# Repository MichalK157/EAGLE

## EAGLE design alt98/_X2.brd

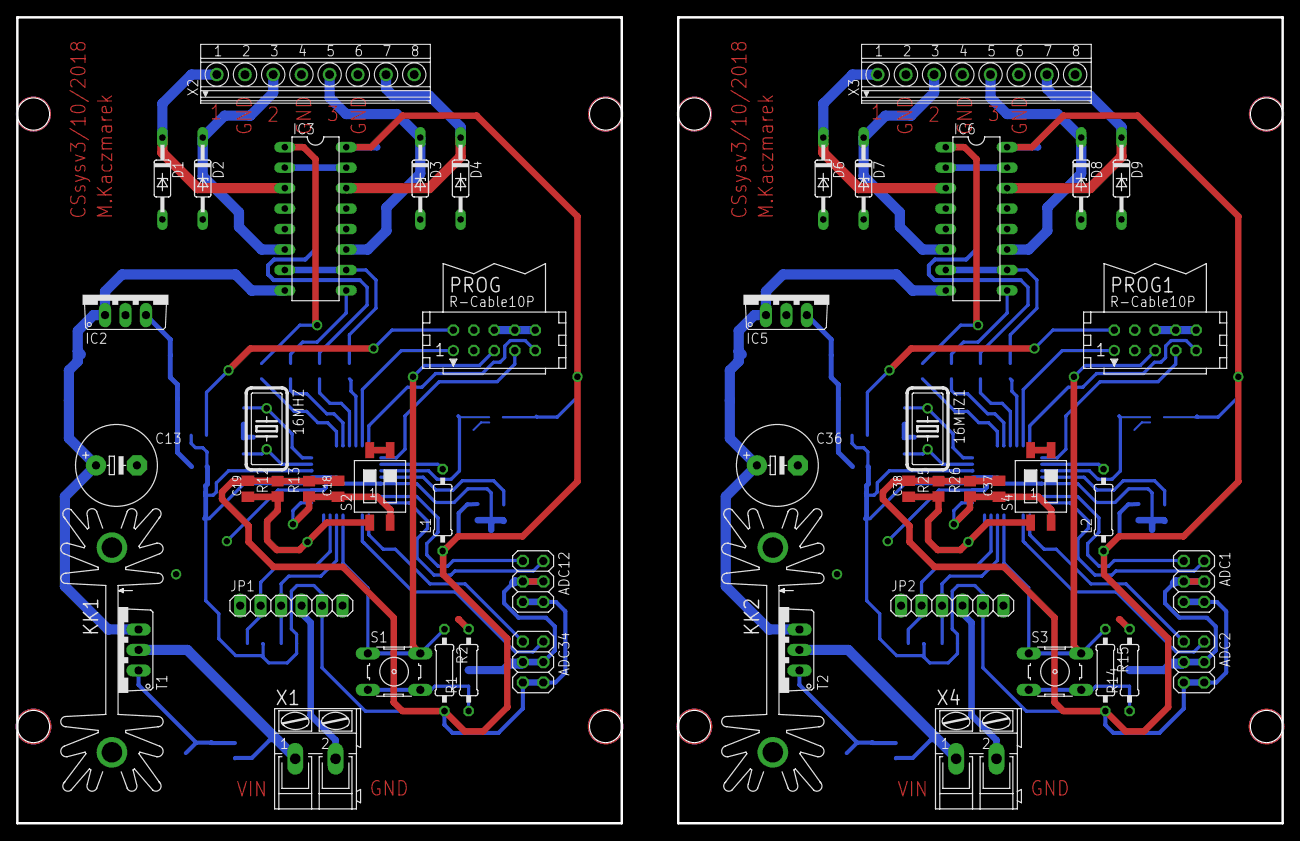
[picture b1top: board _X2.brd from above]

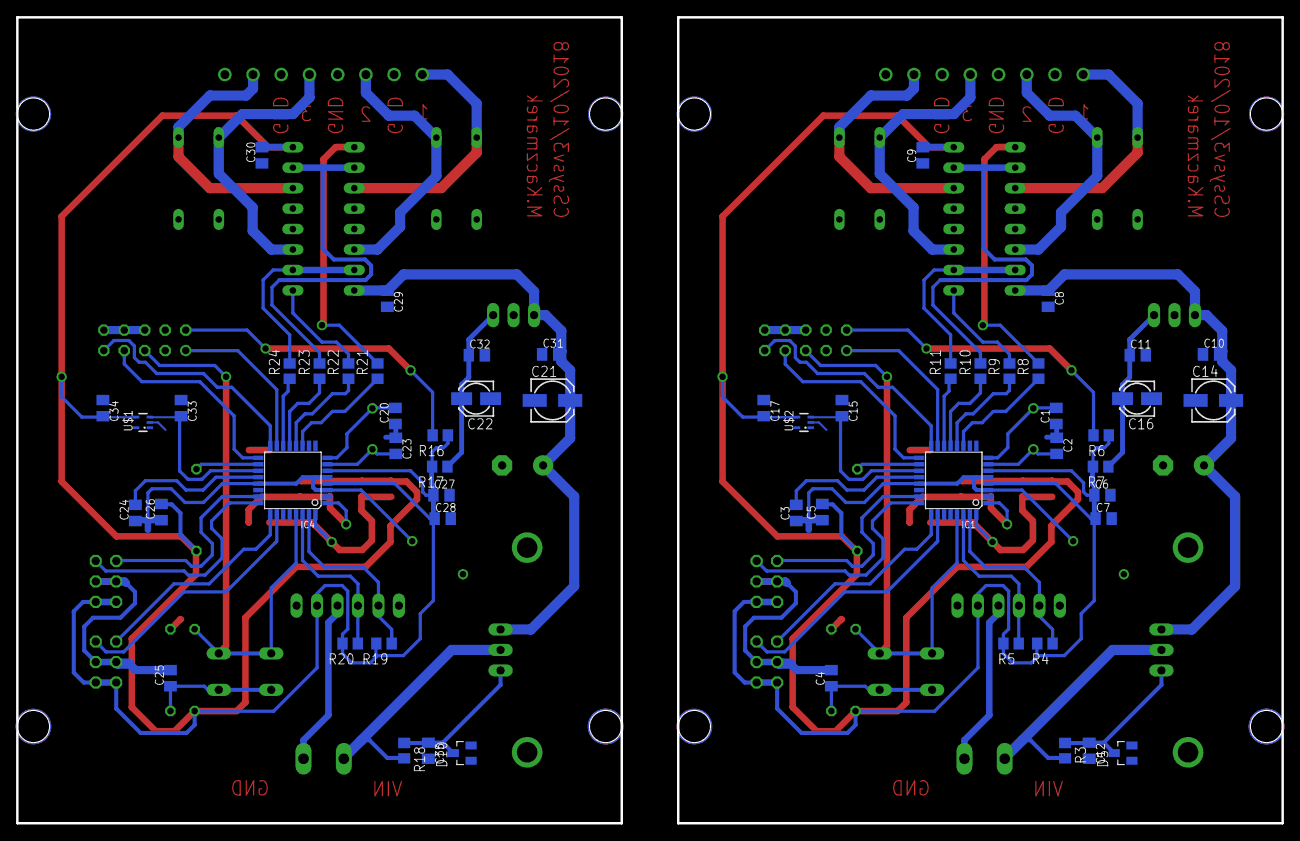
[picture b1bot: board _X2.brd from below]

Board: 2 copper layers, 157.0 x 100.0 mm, 106 parts (56 on the bottom side), 74 nets.

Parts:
16MHZ, 16MHZ1: HC18U-V
ADC1, ADC12: ADC01; 2X03
ADC2, ADC34: ADC23; 2X03
C1, C2, C15, C17, C20, C23, C33, C34: 22P; C0805K
C3, C4, C5, C6, C7, C9, C10, C11, C18, C19, C24, C25, C26, C27, C28, C30, C31, C32, C37, C38: 100n; C0805K
C8, C29: 1u; C0805K
C12, C35: 1uF; C0805K
C13, C36: 470uF; E5-10,5
C14, C21: 10u; 153CLV-0505
C16, C22: 1u; 153CLV-0405
D1, D2, D3, D4, D6, D7, D8, D9: DO35Z10
D5, D10: 13V; SOT23
IC1, IC4: MEGA8-AI; TQFP32-08
IC2, IC5: 7805TV; TO220V
IC3, IC6: L293D; DIL16
JP1, JP2: UART; 1X06
KK1, KK2: SK104-PAD
L1, L2: 10u; 0207/10
PROG, PROG1: SPI-Prog; CON10
R1, R14: 100; 0207/10
R2, R15: 10k; 0207/10
R3, R18: 1.1k; R0805
R4, R5, R19, R20: 4,7k; R0805
R6, R7, R16, R17: 0; R0805
R8, R9, R10, R11, R21, R22, R23, R24: 1k; R0805
R12, R13, R25, R26: 10k; R0805
S1, S3: B3F-10XX
S2, S4: SWS002; SMS-002
T1, T2: ST13007; TO220AV
U$1, U$2: MCP9701; SC70-5L
X1, X4: AK300/2
X2, X3: 1751303

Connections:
1Y: D1.C, IC3.3, X2.1
1Y1: D6.C, IC6.3, X3.1
2Y: D2.C, IC3.6, X2.3
2Y1: D7.C, IC6.6, X3.3
3Y: D3.C, IC3.11, X2.5
3Y1: D8.C, IC6.11, X3.5
4Y: D4.C, IC3.14, X2.7
4Y1: D9.C, IC6.14, X3.7
12EN: IC3.1, R8.2
12EN1: IC6.1, R21.2
34EN: IC3.9, R9.2
34EN1: IC6.9, R22.2
ADC1: ADC12.1, IC1.23
ADC2: ADC12.2, IC1.24
ADC3: ADC34.1, IC1.25
ADC4: ADC34.2, IC1.26
ADC5: ADC2.1, IC4.25
ADC6: C15.2, IC1.19, U$2.3
ADC7: ADC1.1, IC4.23
ADC8: ADC1.2, IC4.24
ADC9: ADC2.2, IC4.26
ADC10: C33.2, IC4.19, U$1.3
AREF: C3.2, IC1.20
AREF1: C24.2, IC4.20
AVCC: IC1.18, L1.2
AVCC1: IC4.18, L2.2
GND: ADC12.3, ADC12.4, ADC34.3, ADC34.4, C1.1, C2.1, C3.1, C4.2, C5.1, C6.2, C7.2, C8.2, C9.1, C10.1, C11.2, C12.2, C13.-, C14.-, C15.1, C16.-, C17.1, D1.A, D2.A, D3.A, D4.A, D5.1, IC1.3, IC1.5, IC1.21, IC2.2, IC3.4, IC3.5, IC3.12, IC3.13, JP1.4, PROG.4, PROG.6, PROG.8, PROG.10, R1.2, S2.3, S2.4, U$2.2, X1.2, X2.2, X2.4, X2.6, X2.8
GND1: ADC1.3, ADC1.4, ADC2.3, ADC2.4, C20.1, C21.-, C22.-, C23.1, C24.1, C25.2, C26.1, C27.2, C28.2, C29.2, C30.1, C31.1, C32.2, C33.1, C34.1, C35.2, C36.-, D6.A, D7.A, D8.A, D9.A, D10.1, IC4.3, IC4.5, IC4.21, IC5.2, IC6.4, IC6.5, IC6.12, IC6.13, JP2.4, PROG1.4, PROG1.6, PROG1.8, PROG1.10, R14.2, S4.3, S4.4, U$1.2, X3.2, X3.4, X3.6, X3.8, X4.2
MISO: IC1.16, PROG.9
MISO1: IC4.16, PROG1.9
MOSI: IC1.15, PROG.1
MOSI1: IC4.15, PROG1.1
unnamed: 16MHZ.2, C2.2, IC1.7
unnamed: 16MHZ.1, C1.2, IC1.8
unnamed: IC1.14, R11.1
unnamed: IC1.13, R10.1
unnamed: PROG.2, R6.2
unnamed: C4.1, R1.1, S1.3, S1.4
unnamed: R3.2, T1.2, X1.1
unnamed: C12.1, D5.3, R3.1, T1.1
unnamed: IC1.12, R9.1
unnamed: IC1.11, R8.1
unnamed: C19.1, IC1.32, R12.1, S2.1
unnamed: C18.1, IC1.1, R13.1, S2.2
unnamed: 16MHZ1.2, C23.2, IC4.7
unnamed: 16MHZ1.1, C20.2, IC4.8
unnamed: C25.1, R14.1, S3.3, S3.4
unnamed: C22.+, C32.1, IC5.3, R17.1
unnamed: PROG1.2, R16.2
unnamed: R18.2, T2.2, X4.1
unnamed: C35.1, D10.3, R18.1, T2.1
unnamed: IC4.14, R24.1
unnamed: IC4.13, R23.1
unnamed: C11.1, C16.+, IC2.3, R7.1
unnamed: IC4.12, R22.1
unnamed: IC4.11, R21.1
unnamed: C38.1, IC4.32, R25.1, S4.1
unnamed: C37.1, IC4.1, R26.1, S4.2
OC1A: IC3.2, IC3.15, R10.2
OC1A1: IC6.2, IC6.15, R23.2
OC1B: IC3.7, IC3.10, R11.2
OC1B1: IC6.7, IC6.10, R24.2
RST: IC1.29, PROG.5, R2.1, S1.1, S1.2
RST1: IC4.29, PROG1.5, R15.1, S3.1, S3.2
RX: IC1.30, JP1.3, R5.1
RX1: IC4.30, JP2.3, R20.1
SCK: IC1.17, PROG.7
SCK1: IC4.17, PROG1.7
TX: IC1.31, JP1.2, R4.1
TX1: IC4.31, JP2.2, R19.1
VCC: ADC12.5, ADC12.6, ADC34.5, ADC34.6, C5.2, C6.1, C7.1, C9.2, C17.2, C18.2, C19.2, IC1.4, IC1.6, IC3.16, JP1.5, L1.1, R2.2, R4.2, R5.2, R6.1, R7.2, R12.2, R13.2, U$2.4
VCC1: C21.+, C29.1, C31.2, C36.+, IC5.1, IC6.8, T2.3
VCC2: C8.1, C10.2, C13.+, C14.+, IC2.1, IC3.8, T1.3
VCC3: ADC1.5, ADC1.6, ADC2.5, ADC2.6, C26.2, C27.1, C28.1, C30.2, C34.2, C37.2, C38.2, IC4.4, IC4.6, IC6.16, JP2.5, L2.1, R15.2, R16.1, R17.2, R19.2, R20.2, R25.2, R26.2, U$1.4

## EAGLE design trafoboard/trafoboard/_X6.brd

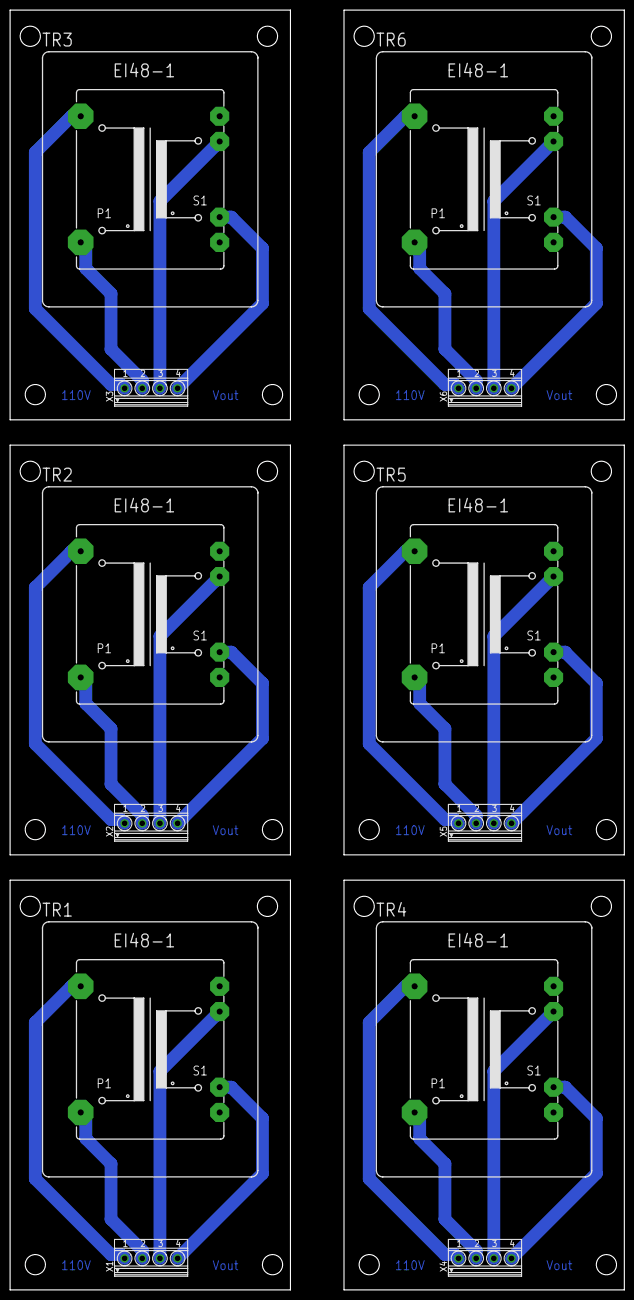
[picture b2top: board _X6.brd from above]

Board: 2 copper layers, 121.7 x 253.6 mm, 12 parts (0 on the bottom side), 24 nets.

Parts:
TR1, TR2, TR3, TR4, TR5, TR6: EI48-1
X1, X2, X3, X4, X5, X6: 1751264

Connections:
unnamed: TR1.1, X1.1
unnamed: TR1.6, X1.2
unnamed: TR1.8, X1.4
unnamed: TR1.11, X1.3
unnamed: TR2.1, X2.1
unnamed: TR2.6, X2.2
unnamed: TR2.8, X2.4
unnamed: TR2.11, X2.3
unnamed: TR3.1, X3.1
unnamed: TR3.6, X3.2
unnamed: TR3.8, X3.4
unnamed: TR3.11, X3.3
unnamed: TR4.1, X4.1
unnamed: TR4.6, X4.2
unnamed: TR4.8, X4.4
unnamed: TR4.11, X4.3
unnamed: TR5.1, X5.1
unnamed: TR5.6, X5.2
unnamed: TR5.8, X5.4
unnamed: TR5.11, X5.3
unnamed: TR6.1, X6.1
unnamed: TR6.6, X6.2
unnamed: TR6.8, X6.4
unnamed: TR6.11, X6.3
